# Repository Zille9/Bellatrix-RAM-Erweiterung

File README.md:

# Bellatrix-RAM-Erweiterung
Zusätzlicher E-RAM für Bellatrix für die Nutzung von CP/M, TRS80-Emulator, Spectrum-Emulator usw.

Diese Platine wird in den Bellatrixsockel des Hive-Computers gesteckt (Bellatrix selbst kommt auf die Erweiterungsplatine. 
Mit ihr ist es möglich die verschiedenen Emulatoren zu nutzen.
TRS80, ZX-Spectrum, Colour-Genie, Nascom.
Beim Hive-Max ist zusätzlich auch die CP/M-Emulation nutzbar.

HINWEIS: der Videoausgang des HIVE-Boards ist bei Verwendung der Ram-Erweiterung nicht mehr nutzbar. Es ist aber mit einem kleinen Umbau möglich, eine alternative Videofunktion zu realisieren (Pins müssen in den Programmen entsprechend angepasst werden Pin16-19). Siehe auch die Skizze TV.jpg

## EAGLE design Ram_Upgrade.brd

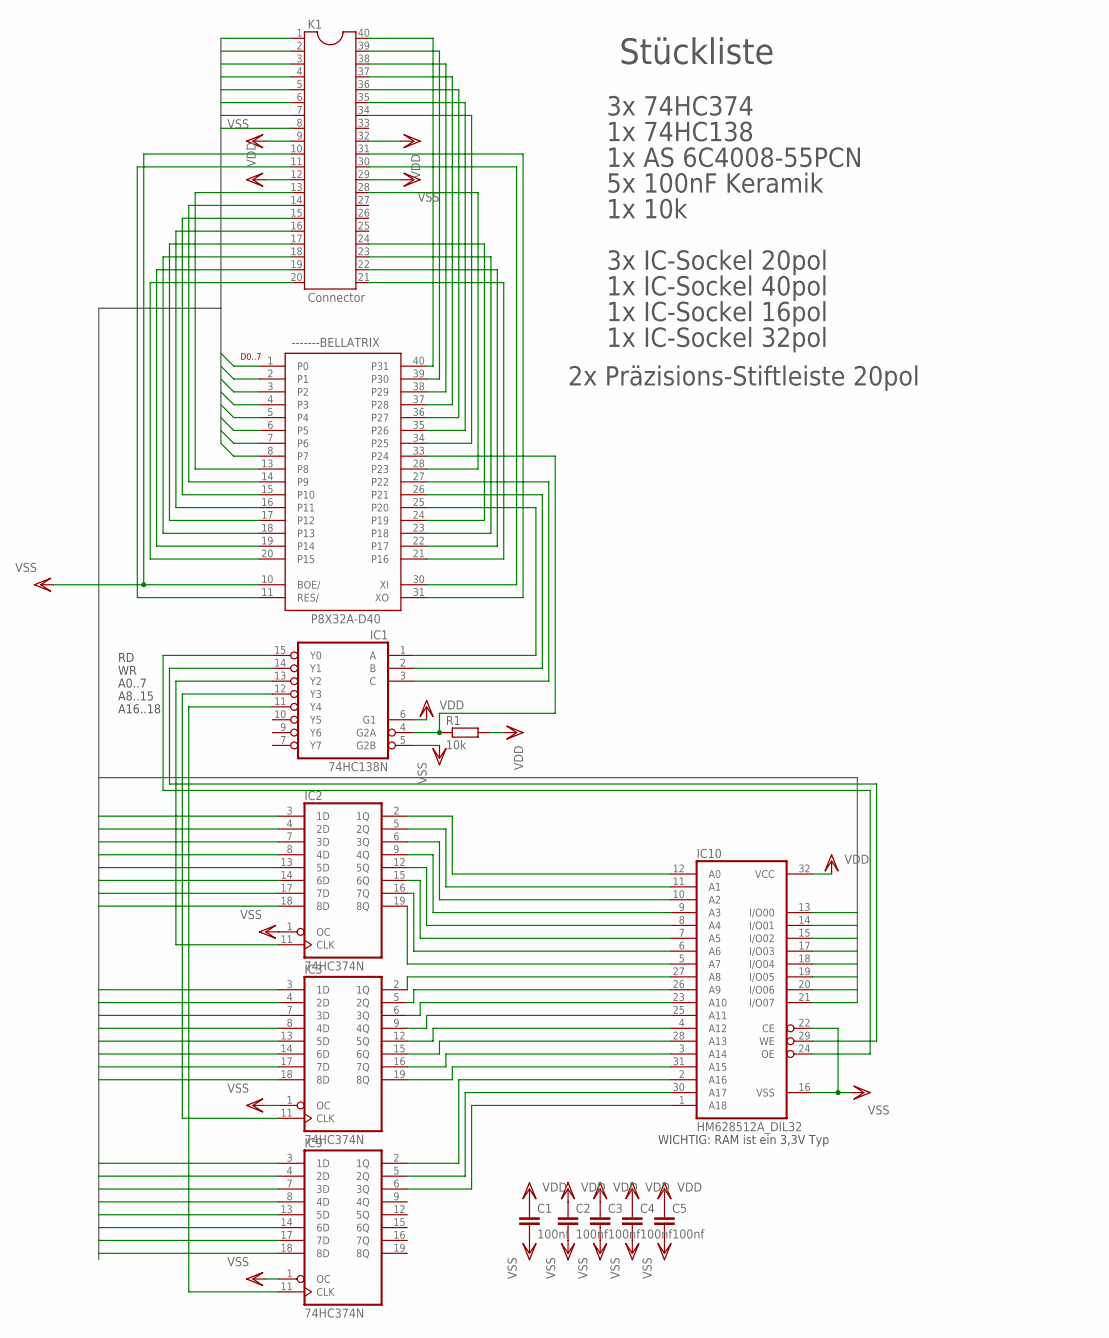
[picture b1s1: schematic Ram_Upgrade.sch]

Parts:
-------BELLATRIX: P8X32A-D40
C1, C2, C3, C4, C5: 100nf; C075-032X103
IC1: 74HC138N; DIL16
IC2, IC3, IC9: 74HC374N; DIL20
IC10: HM628512A_DIL32; DIL32
K1: Connector; DIL40
R1: 10k; 0207/10

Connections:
BUSCLK: -------BELLATRIX.34 (P25), K1.34
D0: -------BELLATRIX.1 (P0), IC2.3 (1D), IC3.3 (1D), IC9.3 (1D), IC10.13 (I/O00), K1.1
D1: -------BELLATRIX.2 (P1), IC2.4 (2D), IC3.4 (2D), IC9.4 (2D), IC10.14 (I/O01), K1.2
D2: -------BELLATRIX.3 (P2), IC2.7 (3D), IC3.7 (3D), IC9.7 (3D), IC10.15 (I/O02), K1.3
D3: -------BELLATRIX.4 (P3), IC2.8 (4D), IC3.8 (4D), IC9.8 (4D), IC10.17 (I/O03), K1.4
D4: -------BELLATRIX.5 (P4), IC2.13 (5D), IC3.13 (5D), IC9.13 (5D), IC10.18 (I/O04), K1.5
D5: -------BELLATRIX.6 (P5), IC2.14 (6D), IC3.14 (6D), IC9.14 (6D), IC10.19 (I/O05), K1.6
D6: -------BELLATRIX.7 (P6), IC2.17 (7D), IC3.17 (7D), IC9.17 (7D), IC10.20 (I/O06), K1.7
D7: -------BELLATRIX.8 (P7), IC2.18 (8D), IC3.18 (8D), IC9.18 (8D), IC10.21 (I/O07), K1.8
GLOB_RESET: -------BELLATRIX.11 (RES/), K1.11
unnamed: -------BELLATRIX.33 (P24), IC1.4 (G2A), R1.1
unnamed: -------BELLATRIX.28 (P23), K1.28
unnamed: -------BELLATRIX.24 (P19), K1.24
unnamed: IC1.13 (Y2), IC2.11 (CLK)
unnamed: -------BELLATRIX.23 (P18), K1.23
unnamed: IC1.12 (Y3), IC3.11 (CLK)
unnamed: IC1.11 (Y4), IC9.11 (CLK)
unnamed: IC2.2 (1Q), IC10.12 (A0)
unnamed: IC2.5 (2Q), IC10.11 (A1)
unnamed: IC2.6 (3Q), IC10.10 (A2)
unnamed: IC2.9 (4Q), IC10.9 (A3)
unnamed: IC2.12 (5Q), IC10.8 (A4)
unnamed: -------BELLATRIX.22 (P17), K1.22
unnamed: IC2.15 (6Q), IC10.7 (A5)
unnamed: IC2.16 (7Q), IC10.6 (A6)
unnamed: IC2.19 (8Q), IC10.5 (A7)
unnamed: -------BELLATRIX.21 (P16), K1.21
unnamed: IC3.2 (1Q), IC10.27 (A8)
unnamed: IC3.5 (2Q), IC10.26 (A9)
unnamed: IC3.6 (3Q), IC10.23 (A10)
unnamed: -------BELLATRIX.13 (P8), K1.13
unnamed: -------BELLATRIX.31 (XO), K1.31
unnamed: -------BELLATRIX.14 (P9), K1.14
unnamed: -------BELLATRIX.15 (P10), K1.15
unnamed: IC1.14 (Y1), IC10.29 (WE)
unnamed: IC3.9 (4Q), IC10.25 (A11)
unnamed: IC3.12 (5Q), IC10.4 (A12)
unnamed: -------BELLATRIX.37 (P28), K1.37
unnamed: -------BELLATRIX.38 (P29), K1.38
unnamed: -------BELLATRIX.16 (P11), K1.16
unnamed: -------BELLATRIX.17 (P12), K1.17
unnamed: -------BELLATRIX.30 (XI), K1.30
unnamed: -------BELLATRIX.18 (P13), K1.18
unnamed: -------BELLATRIX.19 (P14), K1.19
unnamed: -------BELLATRIX.20 (P15), K1.20
unnamed: IC3.15 (6Q), IC10.28 (A13)
unnamed: IC3.16 (7Q), IC10.3 (A14)
unnamed: IC3.19 (8Q), IC10.31 (A15)
unnamed: IC9.2 (1Q), IC10.2 (A16)
unnamed: IC9.5 (2Q), IC10.30 (A17)
unnamed: IC9.6 (3Q), IC10.1 (A18)
unnamed: -------BELLATRIX.36 (P27), K1.36
unnamed: IC1.15 (Y0), IC10.24 (OE)
unnamed: -------BELLATRIX.25 (P20), IC1.1 (A)
unnamed: -------BELLATRIX.26 (P21), IC1.2 (B)
unnamed: -------BELLATRIX.27 (P22), IC1.3 (C)
RX-H1: -------BELLATRIX.40 (P31), K1.40
TX-H1: -------BELLATRIX.39 (P30), K1.39
VDD: -------BELLATRIX.12 (VDD), -------BELLATRIX.32 (VDD), C1.1, C2.1, C3.1, C4.1, C5.1, IC1.6 (G1), IC1.16 (VDD), IC2.20 (VDD), IC3.20 (VDD), IC9.20 (VDD), IC10.32 (VCC), K1.12, K1.32, R1.2
VSS: -------BELLATRIX.9 (VSS), -------BELLATRIX.10 (BOE/), -------BELLATRIX.29 (VSS), C1.2, C2.2, C3.2, C4.2, C5.2, IC1.5 (G2B), IC1.8 (GND), IC2.1 (OC), IC2.10 (GND), IC3.1 (OC), IC3.10 (GND), IC9.1 (OC), IC9.10 (GND), IC10.16 (VSS), IC10.22 (CE), K1.9, K1.10, K1.29
WR: -------BELLATRIX.35 (P26), K1.35

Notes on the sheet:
D0..7
A0..7
A8..15
A16..18
WICHTIG: RAM ist ein 3,3V Typ
Stückliste
3x 74HC374
1x 74HC138
1x AS 6C4008-55PCN
5x 100nF Keramik
2x Präzisions-Stiftleiste 20pol
3x IC-Sockel 20pol
1x IC-Sockel 40pol
1x IC-Sockel 16pol
1x IC-Sockel 32pol
1x 10k

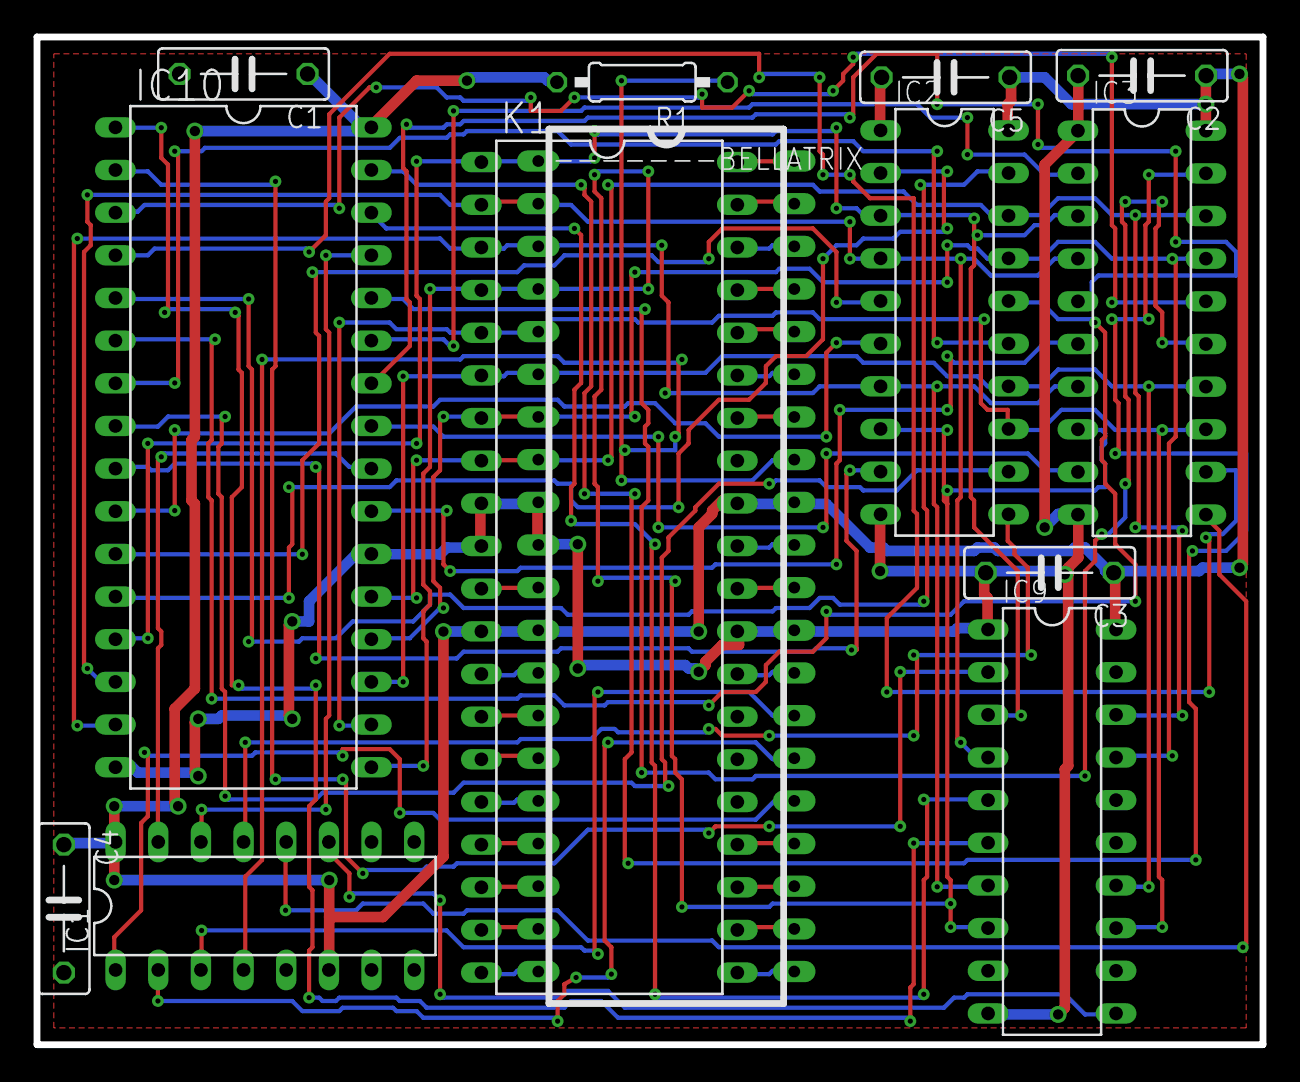
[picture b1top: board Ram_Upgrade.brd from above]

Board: 2 copper layers, 73.0 x 60.0 mm, 13 parts (0 on the bottom side), 61 nets.
